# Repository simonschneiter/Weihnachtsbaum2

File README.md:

# Weihnachtsbaum

_Idea:_
A post card size (A5) PCB in shape of a christmas tree. 
SMD components are already soldered on when sending the postcard. The recipient of the postcard will then need to break apart the mousebites in the PCB, and solder on the THT components for the LEDs and series resistors.

Folder Structure:
- KiCad
  - Orders
  - Gerber
  - Production
- STM32

## Changes List for Revision 2.0 (Oct 2026)
- Add 9V block connector: Either Keystone 2in1 (MPN 967) or separate male (MPN 261) and female (269) - Done
- Update SMPC to 9V capable type: TPS561243 buck reg 1A.
- Add a diode for preventing 9V to reach USB 5V and destroy USB circuits.
- Change SW1 from unpressed 0, pressed 1 (high=3.3V through 5.1k pull up) - Done
- Add output cap for DC/DC converter (22 uF) - Done
- Make USB connection solder pads between PCBs larger (in 90° corner). - Done
- Add 3.3V on tip of tree for 11448 or 11450 auto color changing LED as option - Done
- Remove library files from project and link to SLib library. - To Do

## General Info

Within each subfolder resides a README.txt that describes the tool setup that is being used.
E.g. for STM32 subfolder expect a description if STM32CubeIDE was used or another toolchain. Plus a desciption of which libraries, extensions etc. were used. All info to be able to recreate the build enviroment for the sources.

Within such folder is recommended to place a subfolder 

- Orders 
	containing e.g. material and parts orders from e.g. DigiKey or Mouser, but also the orders for PCB or 3D print manufacturer

- ProductionData
    contains the actual ZIP folder / production files that were created from KiCad or FreeCad etc. for sending to manufacturing

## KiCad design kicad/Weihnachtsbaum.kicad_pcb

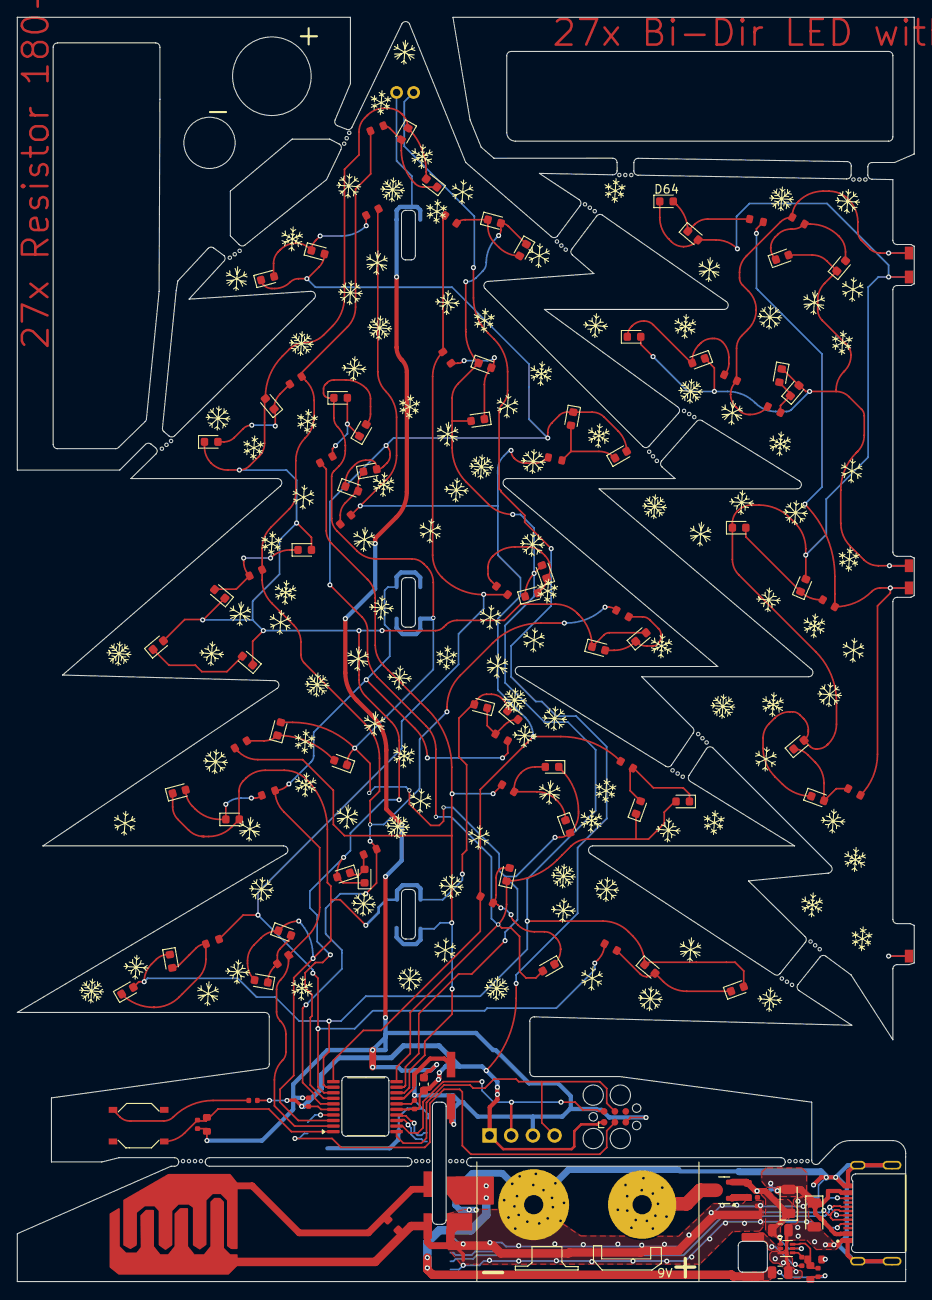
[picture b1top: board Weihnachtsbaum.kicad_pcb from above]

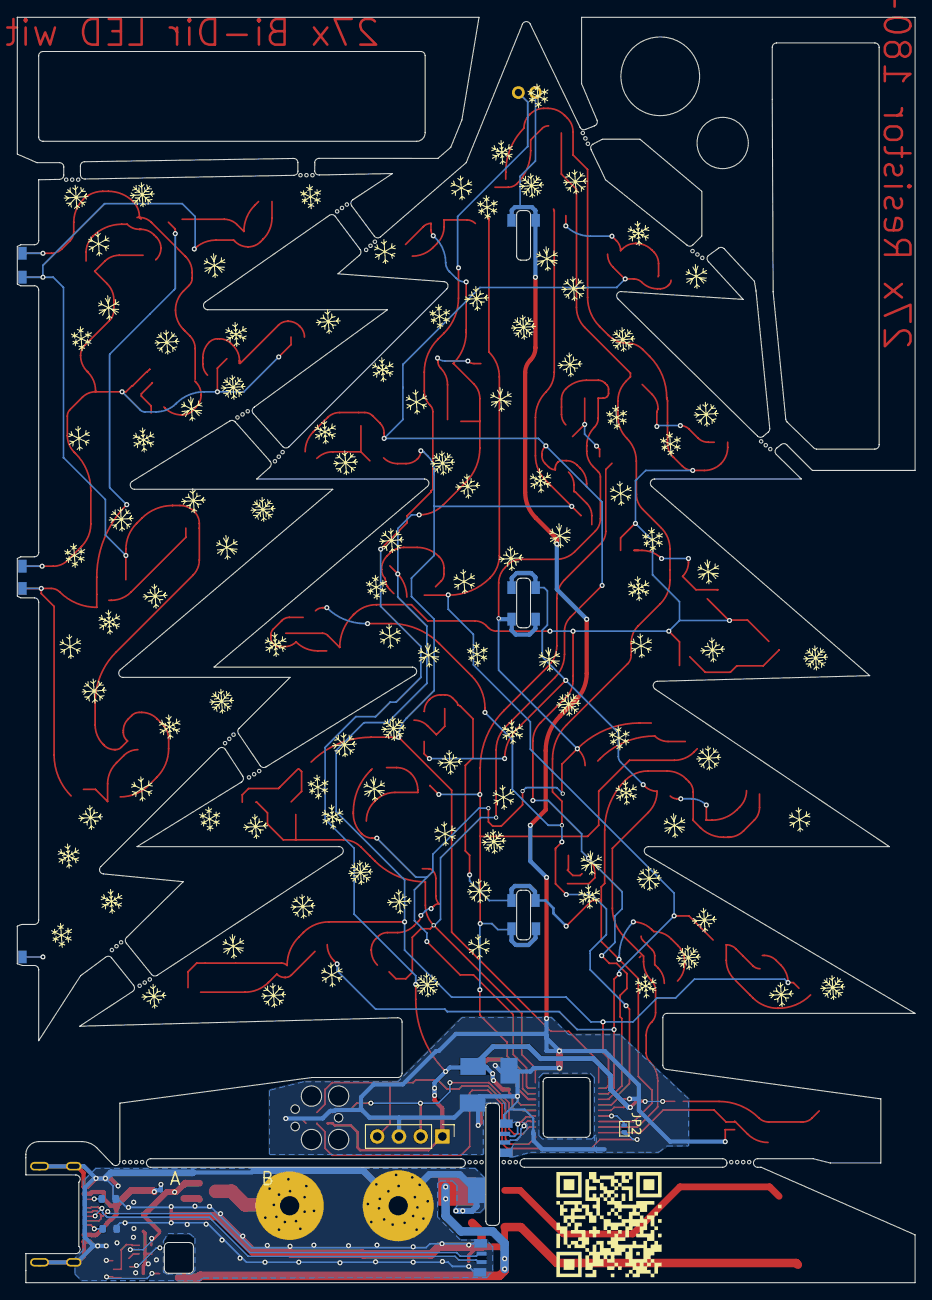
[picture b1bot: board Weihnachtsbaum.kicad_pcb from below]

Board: 2 copper layers, 105.0 x 148.0 mm, 170 parts (32 on the bottom side), 68 nets.

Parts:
BT1: BAT-HOLDER-9V-KEYSTONE967
C1: 10uF / 16V; C_0603_1608Metric
C2, C5, C7: 100nF; C_0402
C3, C9: 22uF / 16V; C_0805_2012Metric
C6: 1.0nF; C_0402
C8: 47pF; C_0402
D1, D4, D5, D6, D13, D14: LED_PURPLE; LED_0603_1608Metric
D2, D8, D10, D12, D15, D16: LED_CYAN; LED_0603_1608Metric
D3, D7, D9, D11, D18, D19, D20: LED_PINK; LED_0603_1608Metric
D17: TouchPad
D27: LED; LED_BIDIR_2PIN_THT_3MM_EDGE
D30: FS22N; D_SOD-123FL
D31, D37, D39, D48, D50, D57, D64, D66: LED_BLUE; LED_0603_1608Metric
D32: SMF5.0A; D_SOD-123FL
D33, D46, D62, D71: LED_GREEN; LED_0603_1608Metric
D34, D38, D45, D51, D55, D61: LED_ORANGE; LED_0603_1608Metric
D35, D40, D44, D47, D53, D56, D60, D63, D67, D68: LED_RED; LED_0603_1608Metric
D36, D41, D49, D52, D58, D59, D65, D69, D70: LED_YELLOW; LED_0603_1608Metric
G1: LOGO; QR-Code-Dirtybit-WBaum-14mm
J1: Conn_01x04; PinHeader_1x04_P2.54mm_Vertical
J2: Conn_ARM_SWD_TagConnect_TC2030; Tag-Connect_TC2030-IDC-FP_2x03_P1.27mm_Vertical
J3: USB4520-03-0-A_REVA; GCT_USB4520-03-0-A_REVA
J10, J11, J12, J13: SMD_SOLDER_PAD_1.2x0.5mm
J14, J15, J16, J17, J30, J31, J32, J33, J34, J35, J36, J37, J40, J41, J42, J43, J44, J45, J46, J47, J50, J51, J52, J53: SMD_SOLDER_PAD_1.5x1mm
J20, J21, J22, J23, J24, J25: SMD_SOLDER_PAD_3x2mm
J70, J71, J72, J73: SMD_SOLDER_PAD_3x1mm
JP2: SolderJumper_2_Open; SolderJumper-2_P1.2mm_Open_RoundedPad0.5x1.0mm
L1: 3.3uH; L_1210_3225_INBOARD
M1, M4: MouseBites4
M2, M3, M5, M6, M7, M8, M9, M10, M11, M12, M13, M14, M15, M16, M17: MouseBites3
Q1: AO3401A; Q_SOT-23
R1, R2, R3, R4, R5, R6, R7, R8, R9, R10, R11, R12, R13, R14, R15, R16, R23, R24, R25, R26, R27, R28, R29, R30, R31, R35, R36: 200R; R_0603
R17: 1k; R_0402
R18: 1M; R_0603
R20, R37: 82k; R_0603
R21: 18k; R_0603
R32, R33: 5.1k; R_0603
R38: 82k; R_0402
R39: 0R; R_0603
SW1: SMD-BUTTON_4P-5.2X5.2X1.5MM-SKQGADE010_; SKQGADE010
U1: STM32F042F6P6-REVERSE-INBOARD
U3: TPS561243; SOT-563

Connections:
3V0: C1.1, C2.1, C5.1, D27.2, J1.1, J2.1 (VCC), J21.1 (1_1), R17.2, U1.5 (VDDA), U1.16 (VDD)
3V0_OUT: C8.2, C9.1, J20.1 (1_1), L1.2, R20.2
5V0_USB: D30.2 (A), D32.1 (K), J3.A4_B9 (VBUS_A), J3.B4_A9 (VBUS_B)
5V_9V_IN: C3.1, D30.1 (K), Q1.2 (S), R39.2, U3.1 (VIN), U3.5 (EN)
/ARM1_A: R1.1, R2.1, R3.1, R4.1, R5.1, U1.6 (PA0)
/ARM1_B: D1.1 (K), D15.2 (A), D20.1 (K), D31.2 (A), D33.1 (K), D34.2 (A), D35.1 (K), D36.2 (A), D37.1 (K), D38.2 (A), D40.2 (A), D41.1 (K), U1.7 (PA1)
/ARM2_A: R6.1, R7.1, R8.1, R9.1, R10.1, U1.8 (PA2)
/ARM2_B: D4.1 (K), D16.2 (A), D18.2 (A), D39.2 (A), D44.2 (A), D45.2 (A), D46.1 (K), D47.1 (K), D48.1 (K), D49.1 (K), U1.9 (PA3)
/ARM3_A: R11.1, R12.1, R13.1, R14.1, R15.1, U1.10 (PA4)
/ARM3_B: D2.1 (K), D3.2 (A), D5.1 (K), D19.2 (A), D51.2 (A), D52.2 (A), D53.2 (A), D56.1 (K), D57.1 (K), D58.1 (K), U1.11 (PA5)
/ARM4_A: D9.2 (A), D10.1 (K), D13.2 (A), D66.2 (A), D67.1 (K), D69.1 (K), J34.1, J36.1, U1.12 (PA6)
/ARM4_A_X: D11.2 (A), D12.1 (K), D14.2 (A), D68.1 (K), D70.1 (K), D71.2 (A), J35.1, J37.1
/ARM4_B: J30.1, J32.1, R16.1, R23.1, R24.1, U1.13 (PA7)
/ARM4_B_X: J31.1, J33.1, R25.1, R26.1, R36.1
/ARM5_A: J41.1, J43.1, R30.1, R31.1, R35.1, U1.2 (PF0)
/ARM5_A_X: J40.1, J42.1, R27.1, R28.1, R29.1
/ARM5_B: D6.1 (K), D7.2 (A), D8.1 (K), D60.2 (A), D61.2 (A), D65.1 (K), J45.1, J47.1, U1.3 (PF1)
/ARM5_B_X: D50.2 (A), D55.2 (A), D59.2 (A), D62.1 (K), D63.1 (K), D64.1 (K), J44.1, J46.1
/BAT_P: BT1.P, Q1.3 (D)
/SW: C7.2, L1.1, U3.2 (SW)
/SWCLK: J1.4, J2.4 (SWCLK), U1.20 (SYS_SWCLK)
/SWDIO: J1.2, J2.2 (SWDIO), U1.19 (SYS_SWDIO)
/TOUCH: J70.1, U1.14 (PB1)
/TOUCHB: D17.2, J71.1, R18.2
/USB_CONN_D_N: J3.A7 (DN1), J3.B7 (DN2), J10.1
/USB_CONN_D_P: J3.A6 (DP1), J3.B6 (DP2), J12.1
/USB_N: J11.1, U1.17 (USB_DM (PA11))
/USB_P: J13.1, U1.18 (USB_DP (PA12))
/VBST: C7.1, U3.4 (VBST)
/VFB: C8.1, R20.1, R21.2, U3.6 (VFB)
GND: C1.2, C2.2, C5.2, C6.1, D27.1, J1.3, J2.5 (GND), J15.1, J17.1, J23.1 (1_1), J25.1 (1_1), J51.1, J53.1, J72.1, R37.1, U1.15 (VSSA)
GND_C: BT1.N, C3.2, C9.2, D17.1, D32.2 (A), J3.A1_B12 (GND_A), J3.B1_A12 (GND_B), J3.S1 (SHELL_GND), J3.S2 (SHELL_GND_1), J3.S3 (SHELL_GND_2), J3.S4 (SHELL_GND_3), J14.1, J16.1, J22.1 (1_1), J24.1 (1_1), J73.1, R18.1, R21.1, R32.1, R33.1, R38.1, U3.3 (GND)
GND_X: J50.1, J52.1
unnamed: D1.2 (A), D40.1 (K), R4.2
unnamed: D2.2 (A), D3.1 (K), R11.2
unnamed: D4.2 (A), D44.1 (K), R9.2
unnamed: D5.2 (A), D53.1 (K), R14.2
unnamed: D6.2 (A), D60.1 (K), R35.2
unnamed: D7.1 (K), D8.2 (A), R31.2
unnamed: D9.1 (K), D10.2 (A), R16.2
unnamed: D11.1 (K), D12.2 (A), R25.2
unnamed: D13.1 (K), D67.2 (A), R24.2
unnamed: D14.1 (K), D70.2 (A), R26.2
unnamed: D15.1 (K), D20.2 (A), R5.2
unnamed: D16.1 (K), D48.2 (A), R8.2
unnamed: D18.1 (K), D47.2 (A), R7.2
unnamed: D19.1 (K), D58.2 (A), R15.2
unnamed: D31.1 (K), D33.2 (A), R1.2
unnamed: D34.1 (K), D35.2 (A), R2.2
unnamed: D36.1 (K), D37.2 (A), R3.2
unnamed: D38.1 (K), D41.2 (A)
unnamed: D39.1 (K), D46.2 (A), R6.2
unnamed: D45.1 (K), D49.2 (A), R10.2
unnamed: D50.1 (K), D62.2 (A), R27.2
unnamed: D51.1 (K), D56.2 (A), R12.2
unnamed: D52.1 (K), D57.2 (A), R13.2
unnamed: D55.1 (K), D63.2 (A), R28.2
unnamed: D59.1 (K), D64.2 (A), R29.2
unnamed: D61.1 (K), D65.2 (A), R30.2
unnamed: D66.1 (K), D69.2 (A), R23.2
unnamed: D68.2 (A), D71.1 (K), R36.2
unnamed: J2.3 (~RESET), JP2.1 (A)
unnamed: J3.A5 (CC1), R33.2
unnamed: J3.B5 (CC2), R32.2
unnamed: JP2.2 (B), U1.4 (NRST)
unnamed: Q1.1 (G), R38.2, R39.1
unnamed: R17.1, SW1.1 (A0)
unnamed: C6.2, R37.2, SW1.4 (B1), U1.1 (PB8)

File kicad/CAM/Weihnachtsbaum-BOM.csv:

Comment,Designator,Footprint,JLCPCB_PN
TPS561243,U3,Package_TO_SOT_SMD:SOT-563,C42040978
FS22N,D30,SLib:D_SOD-123FL,C22466347
SMF5.0A,D32,SLib:D_SOD-123FL,C920173
47pF,C8,PCM_JLCPCB:C_0402,C277503
1.5nF,C6,PCM_JLCPCB:C_0402,C1523
SMD-BUTTON_4P-5.2X5.2X1.5MM-SKQGADE010_,SW1,SLib:SKQGADE010,C116647
SSSS811101,S1,SLib:SW_SSSS811101,C109335
10uF / 16V,C1,Capacitor_SMD:C_0603_1608Metric,C96446
22uF / 16V,C9,Capacitor_SMD:C_0805_2012Metric,C76637
22uF / 16V,C3,Capacitor_SMD:C_0805_2012Metric,C76637
1M,R18,PCM_JLCPCB:R_0603,C22935
5.1k,R33,PCM_JLCPCB:R_0402,C25905
5.1k,R32,PCM_JLCPCB:R_0402,C25905
5.1k,R17,PCM_JLCPCB:R_0402,C25905
18k,R21,PCM_JLCPCB:R_0402,C25756
82k,R37,PCM_JLCPCB:R_0402,C4142
82k,R20,PCM_JLCPCB:R_0402,C4142
100nF,C7,PCM_JLCPCB:C_0402,C1525
100nF,C5,PCM_JLCPCB:C_0402,C1525
100nF,C2,PCM_JLCPCB:C_0402,C1525
STM32F042F6P6-REVERSE-INBOARD,U1,SLib:STM32F042F6P6-REVERSE-INBOARD,
200R,R36,Resistor_THT:R_Axial_DIN0204_L3.6mm_D1.6mm_P7.62mm_Horizontal,
200R,R35,Resistor_THT:R_Axial_DIN0204_L3.6mm_D1.6mm_P7.62mm_Horizontal,
200R,R31,Resistor_THT:R_Axial_DIN0204_L3.6mm_D1.6mm_P7.62mm_Horizontal,
200R,R30,Resistor_THT:R_Axial_DIN0204_L3.6mm_D1.6mm_P7.62mm_Horizontal,
200R,R29,Resistor_THT:R_Axial_DIN0204_L3.6mm_D1.6mm_P7.62mm_Horizontal,
200R,R28,Resistor_THT:R_Axial_DIN0204_L3.6mm_D1.6mm_P7.62mm_Horizontal,
200R,R27,Resistor_THT:R_Axial_DIN0204_L3.6mm_D1.6mm_P7.62mm_Horizontal,
200R,R26,Resistor_THT:R_Axial_DIN0204_L3.6mm_D1.6mm_P7.62mm_Horizontal,
200R,R25,Resistor_THT:R_Axial_DIN0204_L3.6mm_D1.6mm_P7.62mm_Horizontal,
200R,R24,Resistor_THT:R_Axial_DIN0204_L3.6mm_D1.6mm_P7.62mm_Horizontal,
200R,R23,Resistor_THT:R_Axial_DIN0204_L3.6mm_D1.6mm_P7.62mm_Horizontal,
200R,R16,Resistor_THT:R_Axial_DIN0204_L3.6mm_D1.6mm_P7.62mm_Horizontal,
200R,R15,Resistor_THT:R_Axial_DIN0204_L3.6mm_D1.6mm_P7.62mm_Horizontal,
200R,R14,Resistor_THT:R_Axial_DIN0204_L3.6mm_D1.6mm_P7.62mm_Horizontal,
200R,R13,Resistor_THT:R_Axial_DIN0204_L3.6mm_D1.6mm_P7.62mm_Horizontal,
200R,R12,Resistor_THT:R_Axial_DIN0204_L3.6mm_D1.6mm_P7.62mm_Horizontal,
200R,R11,Resistor_THT:R_Axial_DIN0204_L3.6mm_D1.6mm_P7.62mm_Horizontal,
200R,R10,Resistor_THT:R_Axial_DIN0204_L3.6mm_D1.6mm_P7.62mm_Horizontal,
200R,R9,Resistor_THT:R_Axial_DIN0204_L3.6mm_D1.6mm_P7.62mm_Horizontal,
200R,R8,Resistor_THT:R_Axial_DIN0204_L3.6mm_D1.6mm_P7.62mm_Horizontal,
200R,R7,Resistor_THT:R_Axial_DIN0204_L3.6mm_D1.6mm_P7.62mm_Horizontal,
200R,R6,Resistor_THT:R_Axial_DIN0204_L3.6mm_D1.6mm_P7.62mm_Horizontal,
200R,R5,Resistor_THT:R_Axial_DIN0204_L3.6mm_D1.6mm_P7.62mm_Horizontal,
200R,R4,Resistor_THT:R_Axial_DIN0204_L3.6mm_D1.6mm_P7.62mm_Horizontal,
200R,R3,Resistor_THT:R_Axial_DIN0204_L3.6mm_D1.6mm_P7.62mm_Horizontal,
200R,R2,Resistor_THT:R_Axial_DIN0204_L3.6mm_D1.6mm_P7.62mm_Horizontal,
200R,R1,Resistor_THT:R_Axial_DIN0204_L3.6mm_D1.6mm_P7.62mm_Horizontal,
,M17,SLib:MouseBites3,
,M16,SLib:MouseBites3,
,M15,SLib:MouseBites3,
,M14,SLib:MouseBites3,
,M13,SLib:MouseBites3,
,M12,SLib:MouseBites3,
,M11,SLib:MouseBites3,
,M10,SLib:MouseBites3,
,M9,SLib:MouseBites3,
,M8,SLib:MouseBites3,
,M7,SLib:MouseBites3,
,M6,SLib:MouseBites3,
,M5,SLib:MouseBites3,
,M4,SLib:MouseBites4,
,M3,SLib:MouseBites3,
,M2,SLib:MouseBites3,
,M1,SLib:MouseBites4,
3.3uH,L1,SLib:L_1210_3225_INBOARD,
USB4520-03-0-A_REVA,J3,SLib:GCT_USB4520-03-0-A_REVA,
Conn_01x04,J1,Connector_PinHeader_2.54mm:PinHeader_1x04_P2.54mm_Vertical,
LED BIDIR,D29,SLib:LED_BIDIR_2PIN_THT_3MM_REVERSE_NR2,
LED BIDIR,D28,SLib:LED_BIDIR_2PIN_THT_3MM_REVERSE_NR2,
LED,D27,SLib:LED_BIDIR_2PIN_THT_3MM_EDGE,
LED BIDIR,D26,SLib:LED_BIDIR_2PIN_THT_3MM_REVERSE_NR2,
LED BIDIR,D25,SLib:LED_BIDIR_2PIN_THT_3MM_REVERSE_NR2,
LED BIDIR,D24,SLib:LED_BIDIR_2PIN_THT_3MM_REVERSE_NR2,
LED BIDIR,D23,SLib:LED_BIDIR_2PIN_THT_3MM_REVERSE_NR2,
LED BIDIR,D22,SLib:LED_BIDIR_2PIN_THT_3MM_REVERSE_NR2,
LED BIDIR,D21,SLib:LED_BIDIR_2PIN_THT_3MM_REVERSE_NR2,
LED BIDIR,D20,SLib:LED_BIDIR_2PIN_THT_3MM_REVERSE_NR2,
LED BIDIR,D19,SLib:LED_BIDIR_2PIN_THT_3MM_REVERSE_NR2,
LED BIDIR,D18,SLib:LED_BIDIR_2PIN_THT_3MM_REVERSE_NR2,
LED BIDIR,D16,SLib:LED_BIDIR_2PIN_THT_3MM_REVERSE_NR2,
LED BIDIR,D15,SLib:LED_BIDIR_2PIN_THT_3MM_REVERSE_NR2,
LED BIDIR,D14,SLib:LED_BIDIR_2PIN_THT_3MM_REVERSE_NR2,
LED BIDIR,D13,SLib:LED_BIDIR_2PIN_THT_3MM_REVERSE_NR2,
LED BIDIR,D12,SLib:LED_BIDIR_2PIN_THT_3MM_REVERSE_NR2,
LED BIDIR,D11,SLib:LED_BIDIR_2PIN_THT_3MM_REVERSE_NR2,
LED BIDIR,D10,SLib:LED_BIDIR_2PIN_THT_3MM_REVERSE_NR2,
LED BIDIR,D9,SLib:LED_BIDIR_2PIN_THT_3MM_REVERSE_NR2,
LED BIDIR,D8,SLib:LED_BIDIR_2PIN_THT_3MM_REVERSE_NR2,
LED BIDIR,D7,SLib:LED_BIDIR_2PIN_THT_3MM_REVERSE_NR2,
LED BIDIR,D6,SLib:LED_BIDIR_2PIN_THT_3MM_REVERSE_NR2,
LED BIDIR,D5,SLib:LED_BIDIR_2PIN_THT_3MM_REVERSE_NR2,
LED BIDIR,D4,SLib:LED_BIDIR_2PIN_THT_3MM_REVERSE_NR2,
LED BIDIR,D3,SLib:LED_BIDIR_2PIN_THT_3MM_REVERSE_NR2,
LED BIDIR,D2,SLib:LED_BIDIR_2PIN_THT_3MM_REVERSE_NR2,
LED BIDIR EDGE,D1,SLib:LED_BIDIR_2PIN_THT_3MM_EDGE,
BAT-HOLDER-9V-KEYSTONE967,BT1,SLib:BAT-HOLDER-9V-KEYSTONE967,

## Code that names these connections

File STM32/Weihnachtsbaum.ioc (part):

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Mcu.Name=STM32F042F6Px
Mcu.Package=TSSOP20
Mcu.UserName=STM32F042F6Px
PA0.Signal=GPIO_Output
PA1.Signal=GPIO_Output
PA11.Mode=Device
PA11.Signal=USB_DM
PA12.Mode=Device
PA12.Signal=USB_DP
PA13.Mode=Serial_Wire
PA13.Signal=SYS_SWDIO
PA14.Mode=Serial_Wire
PA14.Signal=SYS_SWCLK
PA2.Signal=GPIO_Output
PA3.Signal=GPIO_Output
PA4.Signal=GPIO_Output
PA5.Signal=GPIO_Output
PA6.Signal=GPIO_Output
PA7.Signal=GPIO_Output
PB1.Signal=GPIO_Output
PB8.Signal=GPIO_Input
PF0-OSC_IN.Signal=GPIO_Output
PF1-OSC_OUT.Signal=GPIO_Output
RCC.SYSCLKFreq_VALUE=40000000
RCC.SYSCLKSource=RCC_SYSCLKSOURCE_PLLCLK
board=custom

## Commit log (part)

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2025-12-21 New folder structure repo.
2025-12-21 Initial SW commit of CubeMX generated files.
2025-12-21 Erste FW version mit 1s pro richtung pro LED branch
2025-12-21 Update README.md
    Edit README for Weihnachtsbaum
2025-12-25 Added code for dimming transitions in bidir leds. Added some to do comment in sch.
